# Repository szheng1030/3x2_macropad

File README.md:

# 3x2_macropad

A 3x2 macro pad design in KiCad from while back, syncing here so I don't lose it.  
Fully routed and in theory set for production, would probably consider rerouting in that case though.

Thanks to ai03's wiki: https://wiki.ai03.com/  
The design does use his compilation library for switches too.

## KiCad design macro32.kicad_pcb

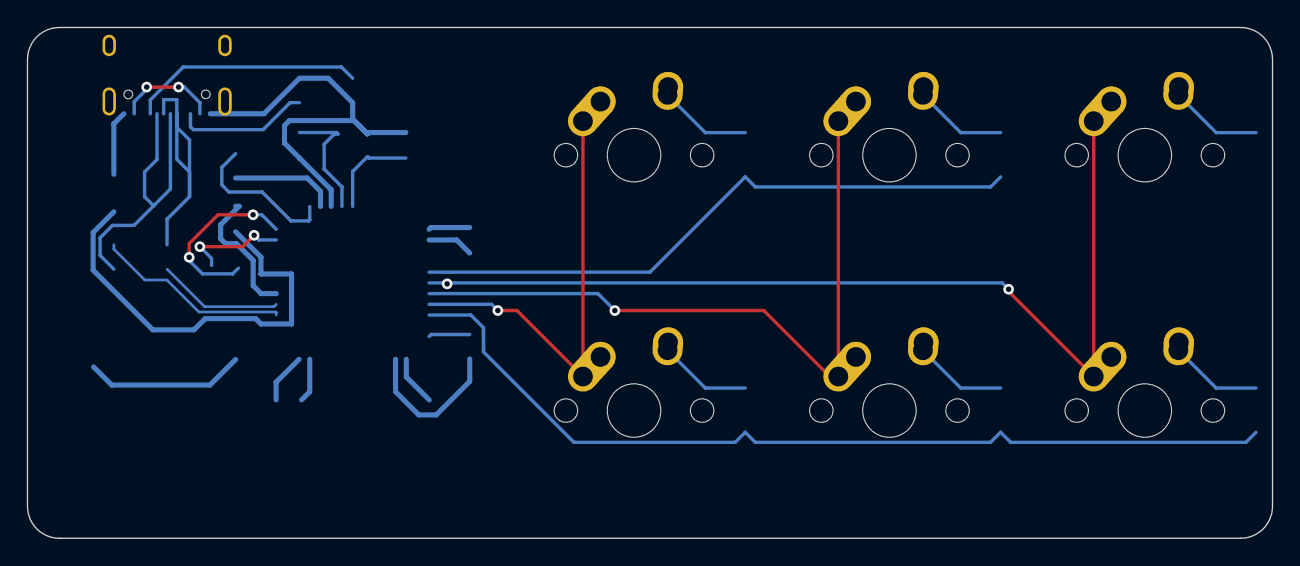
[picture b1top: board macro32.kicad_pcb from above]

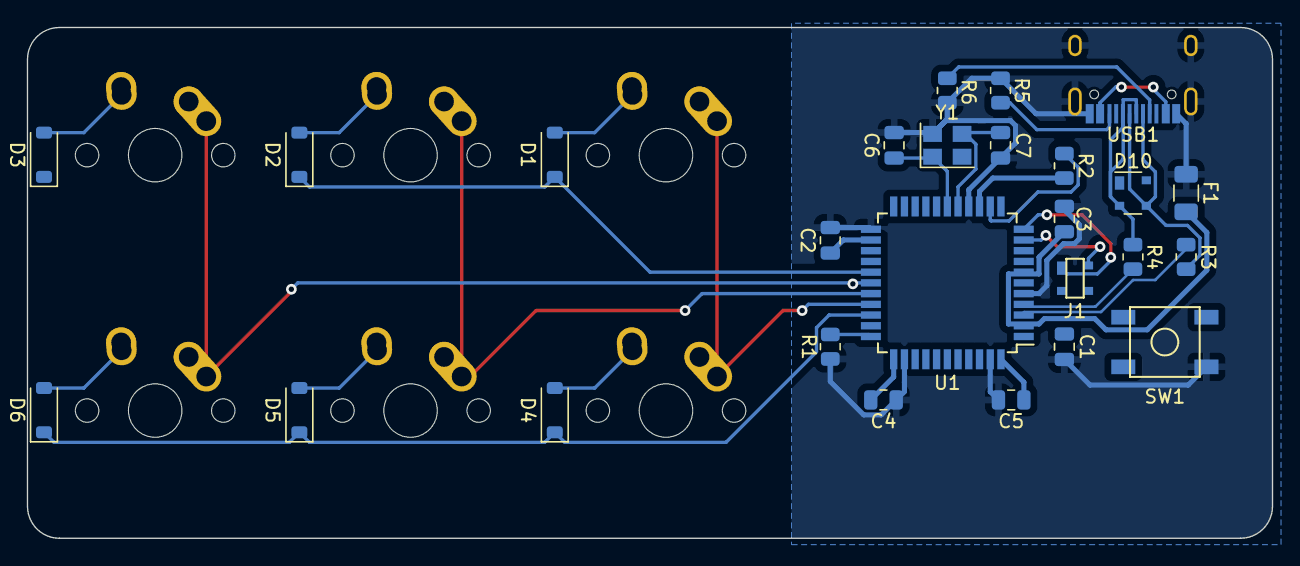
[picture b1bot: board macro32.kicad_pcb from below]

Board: 2 copper layers, 92.9 x 38.1 mm, 32 parts (26 on the bottom side), 28 nets.

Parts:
C1: 1uF; C_0805_2012Metric
C2, C3, C4: 0.1u; C_0805_2012Metric
C5: 10u; C_0805_2012Metric
C6, C7: 22p; C_0805_2012Metric
D1, D2, D3, D4, D5, D6: D_Small; D_SOD-123
D10: PRTR5V0U2X; SOT-143
F1: 500m; Fuse_1206_3216Metric
J1: AVR-ISP-6; SOT143B
MX1, MX2, MX3, MX4, MX5, MX6: MX-NoLED; MX-1U-NoLED
R1, R2: 10k; R_0805_2012Metric
R3, R4: 22; R_0805_2012Metric
R5, R6: 5.1k; R_0805_2012Metric
SW1: SW_Push; SKQG-1155865
U1: ATmega32U4-A; TQFP-44_10x10mm_P0.8mm
USB1: HRO-TYPE-C-31-M-12
Y1: Crystal_GND24_Small; Crystal_SMD_3225-4Pin_3.2x2.5mm

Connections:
+5V: C2.1, C3.1, C4.1, C5.1, F1.2, J1.2 (VCC), R2.1, U1.2 (UVCC), U1.7 (VBUS), U1.14 (VCC), U1.24 (AVCC), U1.34 (VCC), U1.44 (AVCC)
COL0: MX1.1 (COL), MX4.1 (COL), U1.30 (PB6)
COL1: MX2.1 (COL), MX5.1 (COL), U1.29 (PB5)
COL2: MX3.1 (COL), MX6.1 (COL), U1.28 (PB4)
D+: R4.1, U1.4 (D+)
D-: R3.1, U1.3 (D-)
GND: C1.2, C2.2, C3.2, C4.2, C5.2, C6.2, C7.2, D10.1 (GND), F1.1, R1.2, R5.2, R6.2, SW1.1, U1.5 (UGND), U1.15 (GND), U1.23 (GND), U1.35 (GND), U1.43 (GND), USB1.1 (GND), USB1.12 (GND), USB1.13 (SHIELD), Y1.2, Y1.4
MISO: J1.1 (MISO), U1.11 (PB3)
MOSI: J1.4 (MOSI), U1.10 (PB2)
unnamed: D1.2 (A), MX1.2 (ROW)
unnamed: D2.2 (A), MX2.2 (ROW)
unnamed: D3.2 (A), MX3.2 (ROW)
unnamed: D4.2 (A), MX4.2 (ROW)
unnamed: D5.2 (A), MX5.2 (ROW)
unnamed: D6.2 (A), MX6.2 (ROW)
unnamed: D10.2 (I/O1), R4.2, USB1.6 (DP1), USB1.8 (DP2)
unnamed: D10.3 (I/O2), R3.2, USB1.5 (DN2), USB1.7 (DN1)
unnamed: C1.1, U1.6 (UCAP)
unnamed: R1.1, U1.33 (~HWB/PE2)
unnamed: R6.1, USB1.4 (CC1)
unnamed: R5.1, USB1.10 (CC2)
unnamed: USB1.2 (VBUS), USB1.11 (VBUS)
RESET: R2.2, SW1.2, U1.13 (~RESET)
ROW0: D1.1 (K), D2.1 (K), D3.1 (K), U1.27 (PD7)
ROW1: D4.1 (K), D5.1 (K), D6.1 (K), U1.31 (PC6)
SCK: J1.3 (SCK), U1.9 (PB1)
XTAL1: C6.1, U1.17 (XTAL1), Y1.1
XTAL2: C7.1, U1.16 (XTAL2), Y1.3

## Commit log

2024-01-18 Fixed README formatting
2024-01-18 Add KiCad PCB files
